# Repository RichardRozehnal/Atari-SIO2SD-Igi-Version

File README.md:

# Atari SIO2SD Igi Version

SIO2SD je zařízení, které vám umožní nahrávat programy a hry do Atari přes SIO konektor z SD/MMC karty.

## Seznam součástek:

| Ref                      | Qnty | Value                       | Cmp name                    |
|--------------------------|:----:|-----------------------------|-----------------------------|
| C1, C2,                  | 2    | 22pF                        | C_1206                      |
| C9, C8, C7, C6, C5, C4,  | 6    | 22nF                        | C_1206                      |
| C11, C13, C12,           | 3    | 10uF                        | C_Tantal_A/3216             |
| C14, C3, C10,            | 3    | 100nF                       | C_1206                      |
| D1,                      | 1    | LED_Zelená                  | LED_5mm_Zelená              |
| D2,                      | 1    | LED_Žlutá                   | LED_5mm_Žlutá               |
| D3,                      | 1    | LED_Červená                 | LED_5mm_Červená             |
| D4,                      | 1    | LL103A                      | LL103A                      |
| K1,                      | 1    | DRIVE                       | Mikrospínač_6x6x5mm         |
| K2,                      | 1    | NEXT                        | Mikrospínač_6x6x5mm         |
| K3,                      | 1    | CD..                        | Mikrospínač_6x6x5mm         |
| K4,                      | 1    | ENTER                       | Mikrospínač_6x6x5mm         |
| K5,                      | 1    | SHIFT                       | Mikrospínač_6x6x5mm         |
| K6,                      | 1    | RESET                       | Mikrospínač_6x6x5mm         |
| K7,                      | 1    | KF2510-5_Angled_Pitch2.54mm | KF2510-5_Angled_Pitch2.54mm |
| K8,                      | 1    | SD_Card                     | SD_Card                     |
| LCD1,                    | 1    | Display_16x2                | Display_16x2                |
| P1,                      | 1    | 5k                          | 3362P                       |
| R1, R3, R13,             | 3    | 10k                         | R_1206                      |
| R2,                      | 1    | 27R                         | R_1206                      |
| R4, R6, R5,              | 3    | 220R                        | R_1206                      |
| R9, R8, R7,              | 3    | 1k8                         | R_1206                      |
| R11, R12, R10,           | 3    | 3k3                         | R_1206                      |
| U1,                      | 1    | ATMEGA32A-AU                | ATMEGA32A-AU                |
| U2,                      | 1    | HT7533-1                    | HT7533-1                    |
| WP1,                     | 1    | MOSI                        | Wire_Pad                    |
| WP2,                     | 1    | MISO                        | Wire_Pad                    |
| WP3,                     | 1    | SCK                         | Wire_Pad                    |
| WP4,                     | 1    | RST                         | Wire_Pad                    |
| Y1,                      | 1    | 14.318MHz                   | Krystal_HC49-U_Vertical     |

## Fotky hotového výrobku (DPS verze 1):

## Původní autoři zařízení jsou:

Device inventor and AVR software developer: Jakub Kruszona-Zawadzki<br>
ATARI software developer and tester: Paweł Nowak (Pajero/MadTeam)<br>
NVC developer: Marcin Sochacki (Montezuma)<br>
Tester (also new SMD PCB designer - still not finished): Jakub Husak<br>

Tato verze má vylepšené a zjednodušené zapojení od [Igiho](http://blog.3b2.sk/igi/post/SIO2SD-3verzia.aspx).
Otestováno na Atari 800XE a vše funguje bez problému.

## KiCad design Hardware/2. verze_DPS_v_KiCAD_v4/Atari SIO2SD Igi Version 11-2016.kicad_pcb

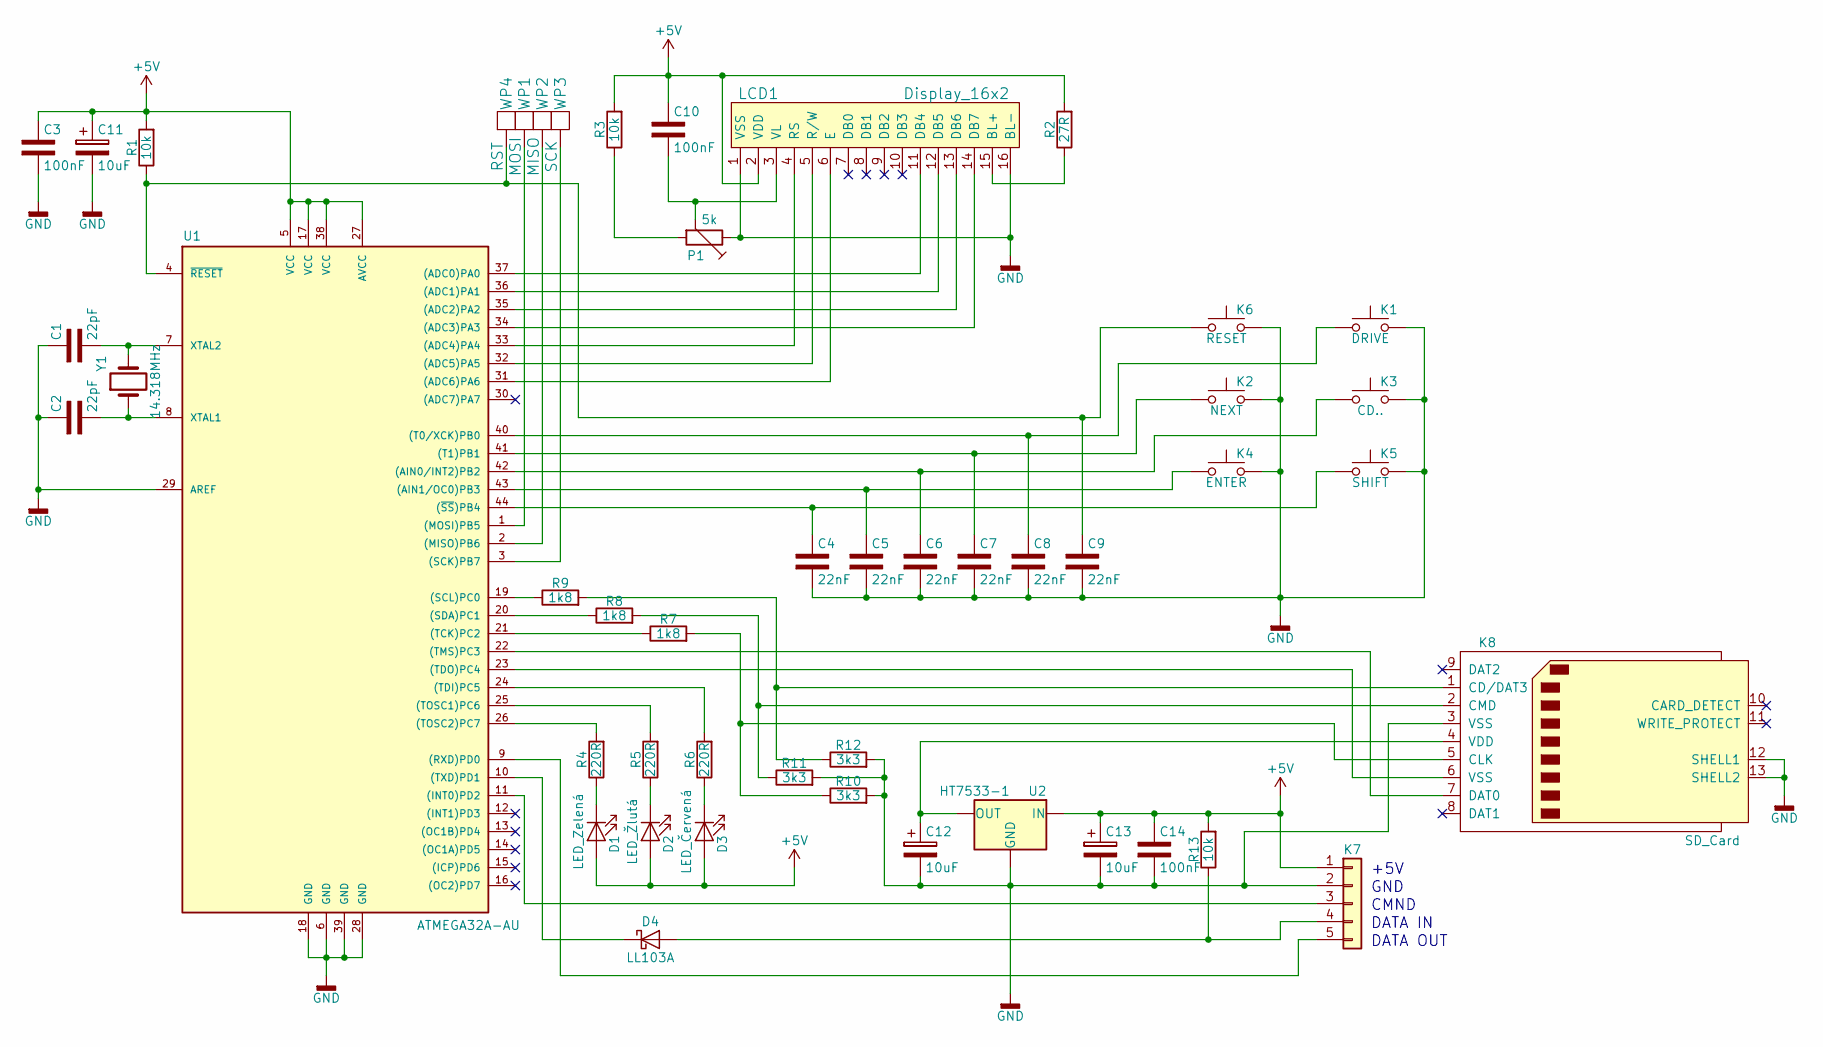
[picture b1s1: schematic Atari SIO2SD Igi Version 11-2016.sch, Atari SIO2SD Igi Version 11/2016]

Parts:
C1, C2: 22pF; C_1206
C3, C10, C14: 100nF; C_1206
C4, C5, C6, C7, C8, C9: 22nF; C_1206
C11, C12, C13: 10uF; CP_Tantalum_Case-A_EIA-3216-18_Reflow
D1: LED_Zelená; LED_D5.0mm
D2: LED_Žlutá; LED_D5.0mm
D3: LED_Červená; LED_D5.0mm
D4: LL103A; D_MiniMELF
K1: DRIVE; SW_PUSH_6mm_h5mm
K2: NEXT; SW_PUSH_6mm_h5mm
K3: CD..; SW_PUSH_6mm_h5mm
K4: ENTER; SW_PUSH_6mm_h5mm
K5: SHIFT; SW_PUSH_6mm_h5mm
K6: RESET; SW_PUSH_6mm_h5mm
K7: KF2510-5_Angled_Pitch2.54mm
K8: SD_Card; SD_Card_Wurth_693061010911
LCD1: Display_16x2; LCD_16x2
P1: 5k; 3362P
R1, R3, R13: 10k; R_1206
R2: 27R; R_1206
R4, R5, R6: 220R; R_1206
R7, R8, R9: 1k8; R_1206
R10, R11, R12: 3k3; R_1206
U1: ATMEGA32A-AU; TQFP-44_10x10mm_Pitch0.8mm
U2: HT7533-1; SOT-89R-3
WP1: MOSI; Wire_Pad_1.27x2.54mm
WP2: MISO; Wire_Pad_1.27x2.54mm
WP3: SCK; Wire_Pad_1.27x2.54mm
WP4: RST; Wire_Pad_1.27x2.54mm
Y1: 14.318MHz; Crystal_HC49-U_Vertical

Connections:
+5V: C3.1, C10.1, C11.1, C13.1, C14.1, D1.2 (A), D2.2 (A), D3.2 (A), K7.1, LCD1.2 (VDD), R1.2, R2.2, R3.2, R13.2, U1.5 (VCC), U1.17 (VCC), U1.27 (AVCC), U1.38 (VCC), U2.2 (IN)
GND: C1.1, C2.1, C3.2, C4.2, C5.2, C6.2, C7.2, C8.2, C9.2, C11.2, C12.2, C13.2, C14.2, K1.2, K2.2, K3.2, K4.2, K5.2, K6.2, K7.2, K8.3 (VSS), K8.12 (SHELL1), K8.13 (SHELL2), LCD1.1 (VSS), LCD1.16 (BL-), P1.3, R10.2, R11.2, R12.2, U1.6 (GND), U1.18 (GND), U1.28 (GND), U1.29 (AREF), U1.39 (GND), U2.1 (GND)
unnamed: C1.2, U1.7 (XTAL2), Y1.2
unnamed: C2.2, U1.8 (XTAL1), Y1.1
unnamed: C4.1, K5.1, U1.44 ((~SS~)PB4)
unnamed: C5.1, K4.1, U1.43 ((AIN1/OC0)PB3)
unnamed: C6.1, K3.1, U1.42 ((AIN0/INT2)PB2)
unnamed: C7.1, K2.1, U1.41 ((T1)PB1)
unnamed: C8.1, K1.1, U1.40 ((T0/XCK)PB0)
unnamed 9: C9.1, K6.1, R1.1, U1.4 (~RESET), WP4.1; also elsewhere on the board
unnamed: C10.2, LCD1.3 (VL), P1.2
unnamed: C12.1, K8.4 (VDD), U2.3 (OUT)
unnamed: D1.1 (K), R4.1
unnamed: D2.1 (K), R5.1
unnamed: D3.1 (K), R6.1
unnamed: D4.1 (K), U1.10 ((TXD)PD1)
unnamed: D4.2 (A), K7.4, R13.1
unnamed: K7.3, U1.11 ((INT0)PD2)
unnamed: K7.5, U1.9 ((RXD)PD0)
unnamed: K8.1 (CD/DAT3), R9.2, R12.1
unnamed: K8.2 (CMD), R8.2, R11.1
unnamed: K8.5 (CLK), R7.2, R10.1
unnamed: K8.6 (VSS), U1.23 ((TDO)PC4)
unnamed: K8.7 (DAT0), U1.22 ((TMS)PC3)
unnamed: LCD1.4 (RS), U1.33 ((ADC4)PA4)
unnamed: LCD1.5 (R/W), U1.32 ((ADC5)PA5)
unnamed: LCD1.6 (E), U1.31 ((ADC6)PA6)
unnamed: LCD1.11 (DB4), U1.37 ((ADC0)PA0)
unnamed: LCD1.12 (DB5), U1.36 ((ADC1)PA1)
unnamed: LCD1.13 (DB6), U1.35 ((ADC2)PA2)
unnamed: LCD1.14 (DB7), U1.34 ((ADC3)PA3)
unnamed: LCD1.15 (BL+), R2.1
unnamed: P1.1, R3.1
unnamed: R4.2, U1.26 ((TOSC2)PC7)
unnamed: R5.2, U1.25 ((TOSC1)PC6)
unnamed: R6.2, U1.24 ((TDI)PC5)
unnamed: R7.1, U1.21 ((TCK)PC2)
unnamed: R8.1, U1.20 ((SDA)PC1)
unnamed: R9.1, U1.19 ((SCL)PC0)
unnamed 47: U1.1 ((MOSI)PB5), WP1.1; also elsewhere on the board
unnamed 48: U1.2 ((MISO)PB6), WP2.1; also elsewhere on the board
unnamed 49: U1.3 ((SCK)PB7), WP3.1; also elsewhere on the board

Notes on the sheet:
+5V
GND
CMND
DATA IN
DATA OUT

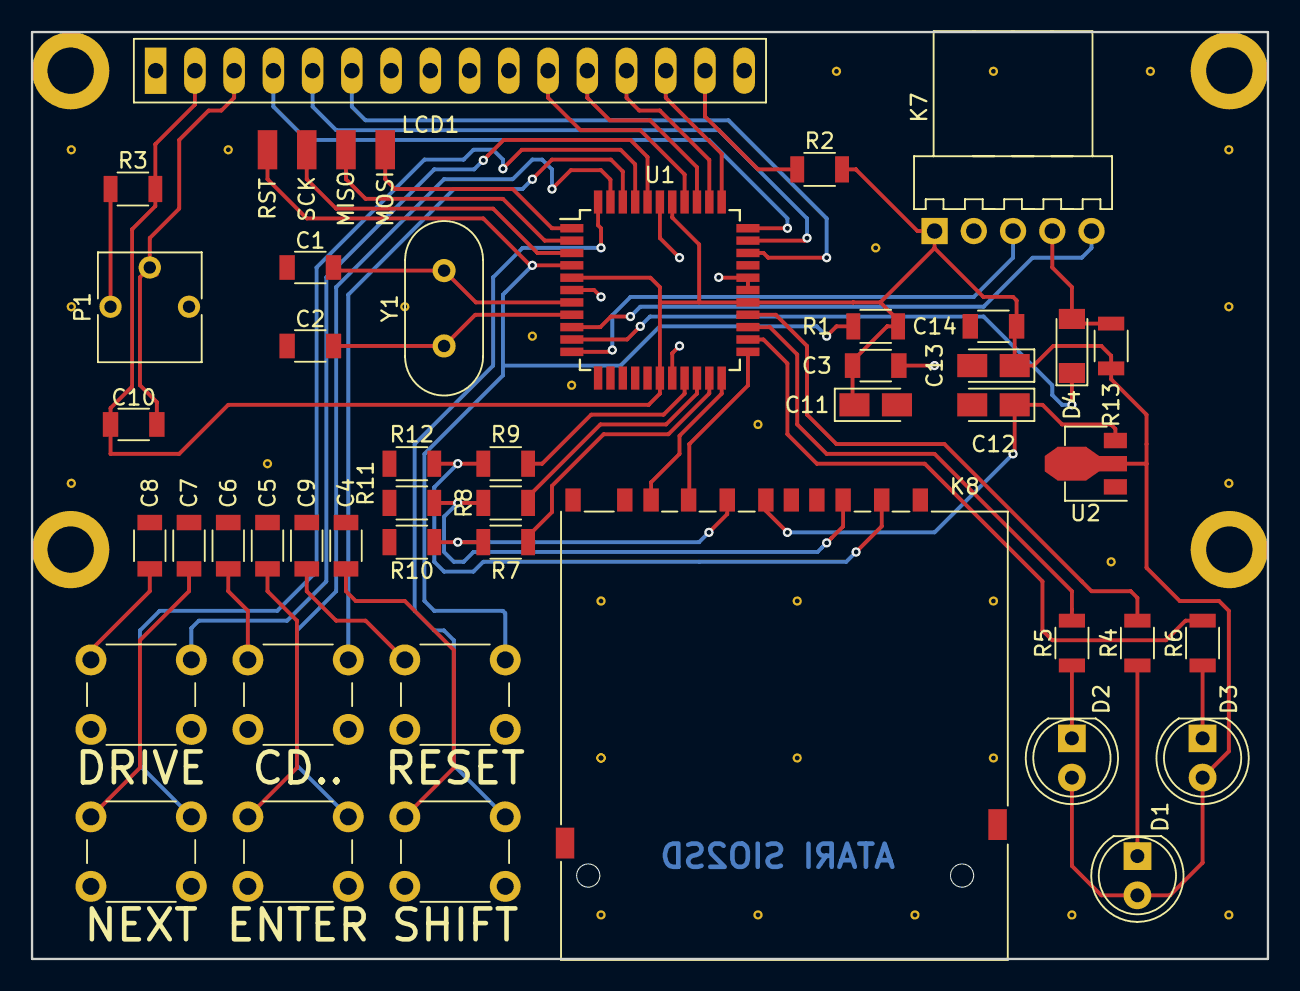
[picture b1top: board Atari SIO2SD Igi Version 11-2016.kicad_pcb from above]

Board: 2 copper layers, 80.0 x 60.0 mm, 48 parts (0 on the bottom side), 42 nets.

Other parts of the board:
MISO: Wire_Pad_1.27x2.54mm
MOSI: Wire_Pad_1.27x2.54mm
RST: Wire_Pad_1.27x2.54mm
SCK: Wire_Pad_1.27x2.54mm

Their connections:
unnamed 9: RST.1; also elsewhere on the board
unnamed 47: MOSI.1; also elsewhere on the board
unnamed 48: MISO.1; also elsewhere on the board
unnamed 49: SCK.1; also elsewhere on the board

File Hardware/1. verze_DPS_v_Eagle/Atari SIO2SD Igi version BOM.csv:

"Qty";"Value";"Device";"Package";"Parts";"Description";"";
"1";"";"693063010911";"693063010911";"J1";"WR-CRD SD CARD CONNECTOR PUSH & PULL WITH CARD DETECTION 9PINS=>Code : Con_I-O_COM_CRD_SD_Normal_693063010911";"";
"1";"";"PSH02-05W";"PSH02-05W";"K1";"Konektory se zamkem - vidlice - 5pin";"";
"4";"";"SMD2";"SMD1,27-2,54";"PAD1, PAD2, PAD3, PAD4";"SMD PAD";"";
"3";"100nF";"C-SMD1206";"1206";"C3, C10, C14";"Kondenzátory keramické SMD 50 V";"";
"3";"10k";"R1206";"R1206";"R1, R3, R13";"Rezistor SMD 1206";"";
"3";"10uF";"CTSA";"A/3216";"C11, C12, C13";"Kondenzátory tantalové - SMD";"";
"3";"1k8";"R1206";"R1206";"R7, R8, R9";"Rezistor SMD 1206";"";
"3";"220R";"R1206";"R1206";"R4, R5, R6";"Rezistor SMD 1206";"";
"6";"22nF";"C-SMD1206";"1206";"C4, C5, C6, C7, C8, C9";"Kondenzátory keramické SMD 50 V";"";
"2";"22pF";"C-SMD1206";"1206";"C1, C2";"Kondenzátory keramické SMD 50 V";"";
"1";"27R";"R1206";"R1206";"R2";"Rezistor SMD 1206";"";
"3";"3k3";"R1206";"R1206";"R10, R11, R12";"Rezistor SMD 1206";"";
"1";"5k";"3362P";"3362P";"P1";"Odporové trimry 3362P";"";
"1";"BAT54S";"BAT54S";"SOT23";"D4";"Schottky";"";
"1";"Display 2x16";"PINHD-1X16";"1X16";"JP1";"PIN HEADER";"";
"1";"HT7533-1";"HT7533-1_SMD";"SOT89R";"IC2";"VOLTAGE REGULATOR";"";
"1";"K1";"10-XX";"B3F-10XX";"DRIVE";"OMRON SWITCH";"";
"1";"K2";"10-XX";"B3F-10XX";"NEXT";"OMRON SWITCH";"";
"1";"K3";"10-XX";"B3F-10XX";"CD..";"OMRON SWITCH";"";
"1";"K4";"10-XX";"B3F-10XX";"ENTER";"OMRON SWITCH";"";
"1";"K5";"10-XX";"B3F-10XX";"SHIFT";"OMRON SWITCH";"";
"1";"K6";"10-XX";"B3F-10XX";"RESET";"OMRON SWITCH";"";
"1";"LED_5MM_CERVENA";"LED_5MM_CERVENA";"A5,0";"D1";"LED 5mm";"";
"1";"LED_5MM_ZELENA";"LED_5MM_ZELENA";"A5,0";"D3";"LED 5mm";"";
"1";"LED_5MM_ZLUTA";"LED_5MM_ZLUTA";"A5,0";"D2";"LED 5mm";"";
"1";"MEGA32-A";"MEGA32-A";"TQFP44";"IC1";"MICROCONTROLLER";"";
"1";"Q14,318MHZ_HC49V";"Q14,318MHZ_HC49V";"HC49U-V";"Q1";"Krystal s pouzdrem HC-49U";"";

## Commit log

2019-08-10 Rename index.d to index.md
2019-08-10 Rename index.md to index.html
2019-08-10 Set theme jekyll-theme-cayman
2019-08-10 Rename index.html to index.md
2020-12-02 Create LICENSE
